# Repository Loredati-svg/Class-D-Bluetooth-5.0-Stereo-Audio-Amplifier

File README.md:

# 🎵 Hi-Fi Class-D Bluetooth 5.0 Stereo Audio Amplifier (2x50W)

A complete Open-Source Hardware project developed in **KiCad 9.0** for building a Hi-Fi **Class-D** stereo audio amplifier featuring an integrated **Bluetooth 5.0 HD** receiver and I2S DAC.

Designed to drive passive speakers with up to **2x50W RMS** output power into a 4Ω load powered by a 24V DC supply.

---

> 🛠️ **Project Status: Active Development**  
> This project is currently **work in progress (WIP)**. Schematics, PCB layout, and documentation are actively being refined and updated. Contributions, suggestions, and feedback are welcome!

---

## 📋 Table of Contents
- [Technical Specifications](#-technical-specifications)
- [Centralized Library Management](#-centralized-library-management)
- [PCB Design and Layout (KiCad)](#-pcb-design-and-layout-kicad)
- [Repository Structure](#-repository-structure)
- [Enclosure & 3D Printing](#-enclosure--3d-printing)
- [License](#-license)

---

## ⚡ Technical Specifications

| Parameter | Value / Specification |
| :--- | :--- |
| **Supply Voltage (DC)** | 24V DC ( 5A recommended for maximum output power) |
| **Main Amplifier IC** | Texas Instruments **TPA3116D2** (Stereo Class-D) |
| **RMS Output Power** | 2 x 50W @ 24V, 4Ω |
| **Power Efficiency** | > 90% (low thermal dissipation) |
| **Bluetooth Module** | Qualcomm **QCC3008** (Bluetooth 5.0, aptX, aptX-LL, A2DP) |
| **Audio DAC** | Texas Instruments **PCM5102A** (24-bit / 192kHz I2S) |
| **Preamp & Tone Control** | Dual Op-Amp **NE5532** / **OPA1612** (Volume, Bass, Treble) |
| **Frequency Response** | 20 Hz – 20 kHz (±0.5 dB) |
| **THD+N (Distortion)** | < 0.1% @ 1W / 1kHz (< 0.05% typical) |
| **Signal-to-Noise Ratio (SNR)** | > 102 dB |
| **Output Reconstruction Filter** | Audiophile-grade shielded LC Low-Pass Filter |
| **Built-in Protections** | Reverse Polarity (P-FET), Overvoltage, Short Circuit, Thermal Shutdown |

---

## 📚 Library Management

This project relies on a dedicated library containing all Symbols, Footprints, 3D Models, and Datasheets.

## 📐 PCB Design and Layout (KiCad)

PCB design choices in KiCad 9.0 adhere to best EMC/EMI and signal integrity practices:

1. **2-Layer Stackup (FR4 - 1.6mm - 1oz/2oz Copper):**
   * **Top Layer:** Audio signal traces, main power routing (high-current power traces > 2.5mm), and SMD components.
   * **Bottom Layer:** Continuous Ground Plane (star grounded, separated into *GND_DIGITAL*, *GND_ANALOG*, and *GND_POWER* with a single star point at the bulk input capacitor).
2. **TPA3116D2 Thermal Dissipation:**
   * Includes an array of **20+ Thermal Vias (0.3mm)** beneath the TPA3116D2 PowerPAD to conduct heat to the bottom copper plane. An extruded aluminum heatsink is attached to the top of the IC.
3. **LC Output Loops:**
   * Physical distance between the TPA3116 output pins, LC filters, and terminal blocks is minimized to prevent traces from acting as EMI radiating antennas.

## 📂 Repository Structure

```text
├── Documentation/                 # Project documentation and guides
├── Gerber/                        # Gerber, Drill, and MAP production files
├── KiCad_Project/
│   ├── Audio_Amp_v1.kicad_pro    # KiCad 8 Project File
│   ├── Audio_Amp_v1.kicad_sch    # Schematic Sheet
│   ├── Audio_Amp_v1.kicad_pcb    # PCB Layout
│   └── Audio_Amp_v1.xml          # Exported BOM
├── libs/
│   └── Kicad_Library/             # Library folder of the project
│       ├── Audio_amplifier/       # Power Amplifier ICs
│       ├── DCDC-converters/       # DC-DC converters
│       ├── Passives               # Passive components (with non standard footprint)
│       └── WIP/                   # WIP
├── Production/                    # Pick&Place (CPL) and JLCPCB BOM files
├── 3D_Print_Case/                 # STL Enclosure models for 3D printing
├── LICENSE                        # CERN-OHL-P License
└── README.md                      # Project Readme
```
---

## 🎨 Enclosure & 3D Printing

The repository includes a custom-designed, fully tailored 3D printable enclosure located in the `/3D_Print_Case` directory. It is engineered to protect the electronics while ensuring adequate passive thermal dissipation and a clean, professional look.

### 🛠️ Key Design Features
* **Front Panel:** Precise cutouts for Volume, Bass, and Treble potentiometers, Power switch, and status LEDs (Power & Bluetooth pairing).
* **Rear Panel:** Dedicated cutouts for high-quality speaker binding posts, DC barrel jack (5.5x2.5mm), and an optional SMA connector for an external Bluetooth antenna.
* **Thermal Management:** Top and bottom passive ventilation slots strategically aligned above the TPA3116D2 heatsink and LC filter inductors to prevent heat buildup.
* **Mechanical Fastening:** Designed for **M3 heat-set brass threaded inserts** (ruthex-style) embedded into internal mounting bosses for repeated assembly without wearing out printed plastic threads.

## 📜 License

This hardware project is released under the **CERN Open Hardware Licence Permissive v2 ([CERN-OHL-P v2](https://ohwr.org/cernohl))**.

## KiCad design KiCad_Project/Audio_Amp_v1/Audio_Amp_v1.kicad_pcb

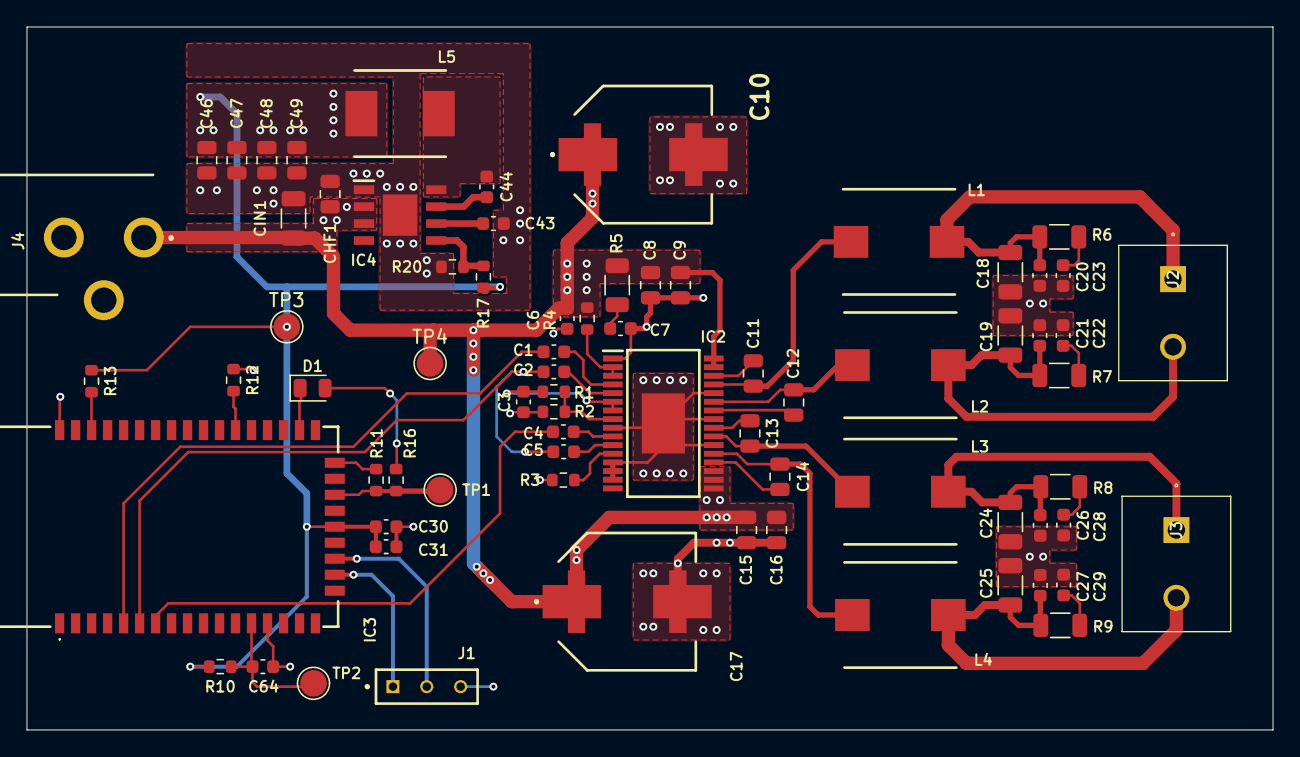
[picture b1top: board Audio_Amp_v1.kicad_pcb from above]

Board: 2 copper layers, 93.5 x 52.8 mm, 73 parts (0 on the bottom side), 44 nets.

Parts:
C1, C2, C3, C4, C5, C30, C43: 1u; C_0603_1608Metric
C6, C22, C23, C28, C29: 10n; C_0603_1608Metric
C7, C31, C64: 100n; C_0603_1608Metric
C8, C15: 1n; C_0805_2012Metric
C9, C16: 100n; C_0805_2012Metric
C10, C17: 220u; EEHZT1E561UV
C11, C12, C13, C14: 220n; C_0805_2012Metric
C18, C19, C24, C25: 680n; C_1206_3216Metric
C20, C21, C26, C27: 1n; C_0603_1608Metric
C44: 0.1u; C_0603_1608Metric
C46, C47, C48, C49: 22u; C_0805_2012Metric
CHF1: 220n; C_0805_2012Metric
CIN1: 10u; C_1206_3216Metric
D1: LED; D_0805_2012Metric
IC2: TPA3116D2DAD; SOP65P810X120-32N
IC3: BM64SPKS1MC2-0002AA; BM64SPKS1MC20002AA
IC4: LMR33630ADDA; SOIC127P600X170-9N
J1: TS-103-T-A; SAMTEC_TS-103-T-A
J2, J3: 1729128
J4: PJ-102AH
L1, L2, L3, L4: 10u; INDPM8479X720N
L5: IHLP2525CZER6R8M8A; INDPM6965X300N
R1, R3, R4, R17: 100k; R_0603_1608Metric
R2: 20k; R_0603_1608Metric
R5, R6, R7, R8, R9: 3.3R; R_1206_3216Metric
R10, R11, R12, R13: 10k; R_0603_1608Metric
R16: 330; R_0603_1608Metric
R20: 43.2k; R_0603_1608Metric
TP1, TP2, TP3, TP4: TestPoint; TestPoint_Pad_D2.0mm

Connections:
+3.3V: C30.1, C31.1, C46.2, C47.2, C48.2, C49.2, IC3.22 (BAT_IN), L5.2, R10.1, R13.1, R17.2, TP3.1 (1_1)
+24V: C6.2, C8.1, C9.1, C10.1, C15.1, C16.1, C17.1, CHF1.1, CIN1.1, IC2.17 (AVCC), IC2.18 (PVCC_1), IC2.19 (PVCC_2), IC2.31 (PVCC_3), IC2.32 (PVCC_4), IC4.2 (VIN), IC4.3 (EN), J4.1, R4.1, R5.1, TP4.1 (1_1)
/02_Bluetooth_Receiver/RST_N: C64.1, IC3.13 (RST_N), R10.2, TP2.1 (1_1)
/02_Bluetooth_Receiver/SYS_PWR: IC3.24 (SYS_PWR), R11.2, R16.2, TP1.1 (1_1)
GNDA: C3.1, C6.1, C7.1, C8.2, C9.2, C10.2, C15.2, C16.2, C17.2, C18.2, C19.1, C20.2, C21.1, C22.1, C23.2, C24.2, C25.1, C26.2, C27.1, C28.2, C29.1, C30.2, C31.2, C43.2, C46.1, C47.1, C48.1, C49.1, C64.2, CHF1.2, CIN1.2, IC2.1 (MODSEL), IC2.9 (GND_1), IC2.13 (AM2), IC2.14 (AM1), IC2.15 (AM0), IC2.22 (GND_2), IC2.25 (GND_3), IC2.28 (GND_4), IC2.33 (GND), IC3.14 (GND_1), IC3.43 (GND_2), IC4.1 (PGND), IC4.9 (AGND), J1.03, J4.2, J4.3, R2.2, R3.1, R12.1, R20.1
IN_COM: C2.1, C5.2, IC3.6 (AOHPM)
IN_P_LEFT: C4.2, IC3.7 (AOHPL)
IN_P_RIGHT: C1.1, IC3.5 (AOHPR)
unnamed: C7.2, R5.2
unnamed: C22.2, R7.1
unnamed: C23.1, R6.2
unnamed: C28.1, R8.2
unnamed: C29.2, R9.1
unnamed: D1.2 (A), R16.1
unnamed: D1.1 (K), IC3.28 (LED1)
unnamed: C14.1, IC2.20 (BSNL)
unnamed: C12.1, IC2.26 (BSNR)
unnamed: C13.1, IC2.24 (BSPL)
unnamed: C11.1, IC2.30 (BSPR)
unnamed: IC2.2 (SDZ), IC2.3 (FAULTZ), R4.2
unnamed: IC2.8 (GAIN/SLV), R1.2, R2.1
unnamed: C3.2, IC2.6 (PLIMIT), IC2.7 (GVDD), R1.1
unnamed: C5.1, IC2.11 (LINN)
unnamed: C4.1, IC2.10 (LINP)
unnamed: IC2.12 (MUTE), R3.2
unnamed: C14.2, IC2.21 (OUTNL), L4.1
unnamed: C12.2, IC2.27 (OUTNR), L2.2
unnamed: C13.2, IC2.23 (OUTPL), L3.1
unnamed: C11.2, IC2.29 (OUTPR), L1.1
unnamed: C2.2, IC2.5 (RINN)
unnamed: C1.2, IC2.4 (RINP)
unnamed: IC3.32 (EAN), R12.2
unnamed: IC3.26 (MFB), R11.1
unnamed: IC3.41 (P2_0), R13.2
unnamed: C44.1, IC4.7 (BOOT)
unnamed: IC4.5 (FB), R17.1, R20.2
unnamed: C44.2, IC4.8 (SW), L5.1
unnamed: C43.1, IC4.6 (VCC)
OUT_N_LEFT: C25.2, C27.2, J3.2, L4.2, R9.2
OUT_N_RIGHT: C19.2, C21.2, J2.2, L2.1, R7.2
OUT_P_LEFT: C24.1, C26.1, J3.1, L3.2, R8.1
OUT_P_RIGHT: C18.1, C20.1, J2.1, L1.2, R6.1
UART_RX: IC3.19 (HCI_RXD), J1.01
UART_TX: IC3.20 (HCI_TXD), J1.02
